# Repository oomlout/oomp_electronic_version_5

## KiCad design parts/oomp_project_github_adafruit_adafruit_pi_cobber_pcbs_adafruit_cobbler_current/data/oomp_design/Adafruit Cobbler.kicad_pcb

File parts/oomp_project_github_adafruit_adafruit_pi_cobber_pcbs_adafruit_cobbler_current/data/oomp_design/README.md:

# OOMP KiCad design copy

Open `Adafruit Cobbler.kicad_pro` (or the `.kicad_pcb` / `.kicad_sch`) in KiCad. Local OOMP libraries are under `libraries/`. Original inputs are preserved in [../original/](../original/).

Only verified unchanged installed KiCad defaults were renamed. Modified, custom, unmatched and unavailable items remain unchanged. Soldering variants are never swapped during conversion. Existing pad coordinates, nets and UUIDs are preserved.

See [conversion_report.yaml](conversion_report.yaml) for every conversion and skip. Copy this directory before editing; regeneration refuses to overwrite edited design files.

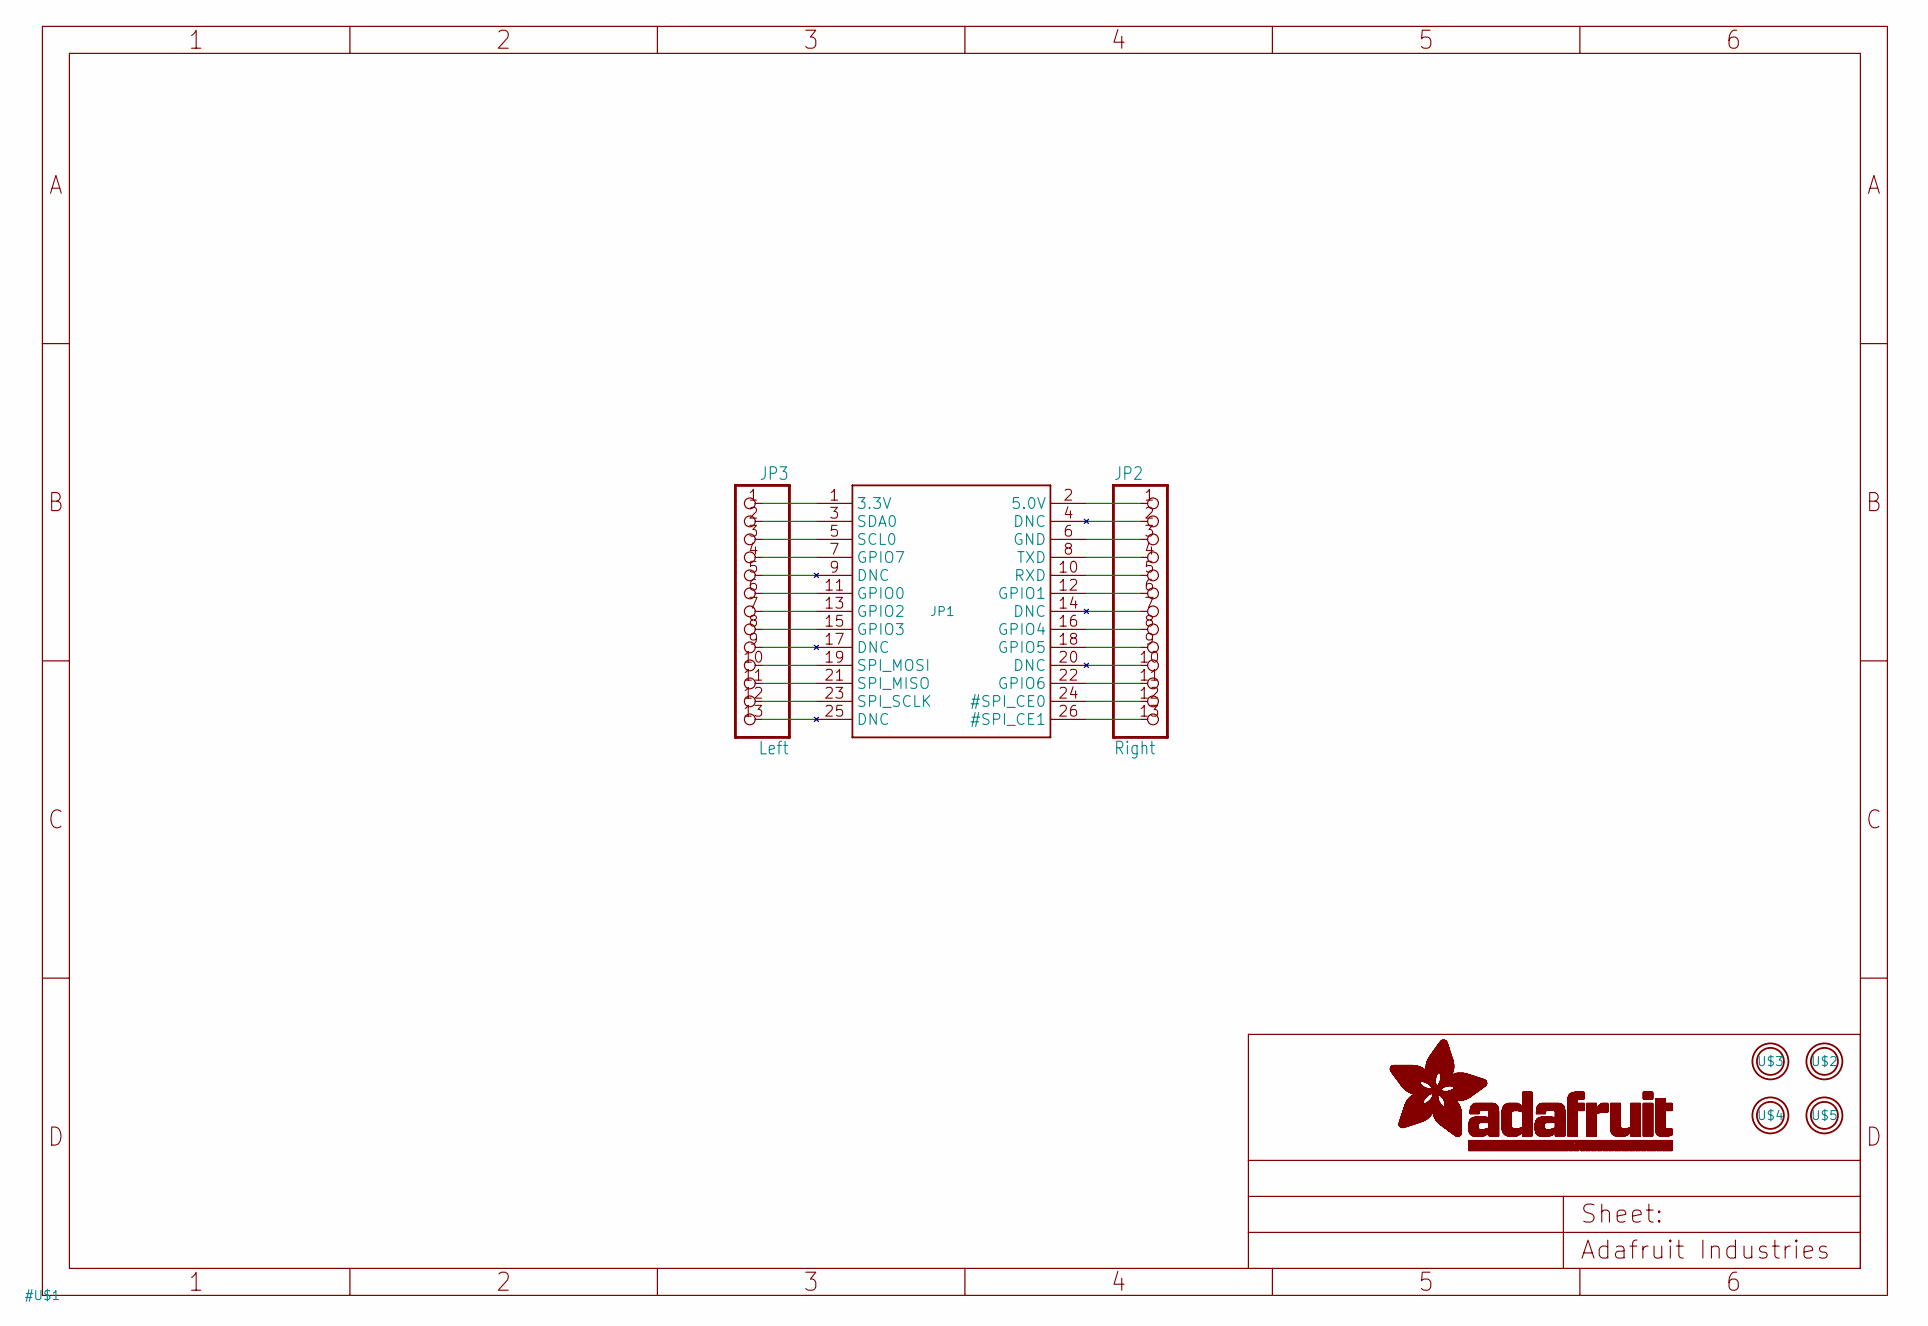
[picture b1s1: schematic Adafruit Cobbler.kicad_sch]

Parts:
JP1: PI; RASBERRYPI_IDC
JP2: Right; 1X13_ROUND_76MIL
JP3: Left; 1X13_ROUND_76MIL
U$2, U$3, U$4, U$5: MOUNTINGHOLE2.5; MOUNTINGHOLE_2.5_PLATED

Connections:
3.3V: JP1.1 (3.3V), JP3.1
5.0V: JP1.2 (5.0V), JP2.1
GND: JP1.6 (GND), JP2.3
unnamed: JP1.3 (SDA0), JP3.2
unnamed: JP1.5 (SCL0), JP3.3
unnamed: JP1.7 (GPIO7), JP3.4
unnamed: JP1.9 (DNC), JP3.5
unnamed: JP1.11 (GPIO0), JP3.6
unnamed: JP1.13 (GPIO2), JP3.7
unnamed: JP1.15 (GPIO3), JP3.8
unnamed: JP1.17 (DNC), JP3.9
unnamed: JP1.19 (SPI_MOSI), JP3.10
unnamed: JP1.21 (SPI_MISO), JP3.11
unnamed: JP1.23 (SPI_SCLK), JP3.12
unnamed: JP1.25 (DNC), JP3.13
unnamed: JP1.4 (DNC), JP2.2
unnamed: JP1.8 (TXD), JP2.4
unnamed: JP1.10 (RXD), JP2.5
unnamed: JP1.12 (GPIO1), JP2.6
unnamed: JP1.14 (DNC), JP2.7
unnamed: JP1.16 (GPIO4), JP2.8
unnamed: JP1.18 (GPIO5), JP2.9
unnamed: JP1.20 (DNC), JP2.10
unnamed: JP1.22 (GPIO6), JP2.11
unnamed: JP1.24 (#SPI_CE0), JP2.12
unnamed: JP1.26 (#SPI_CE1), JP2.13

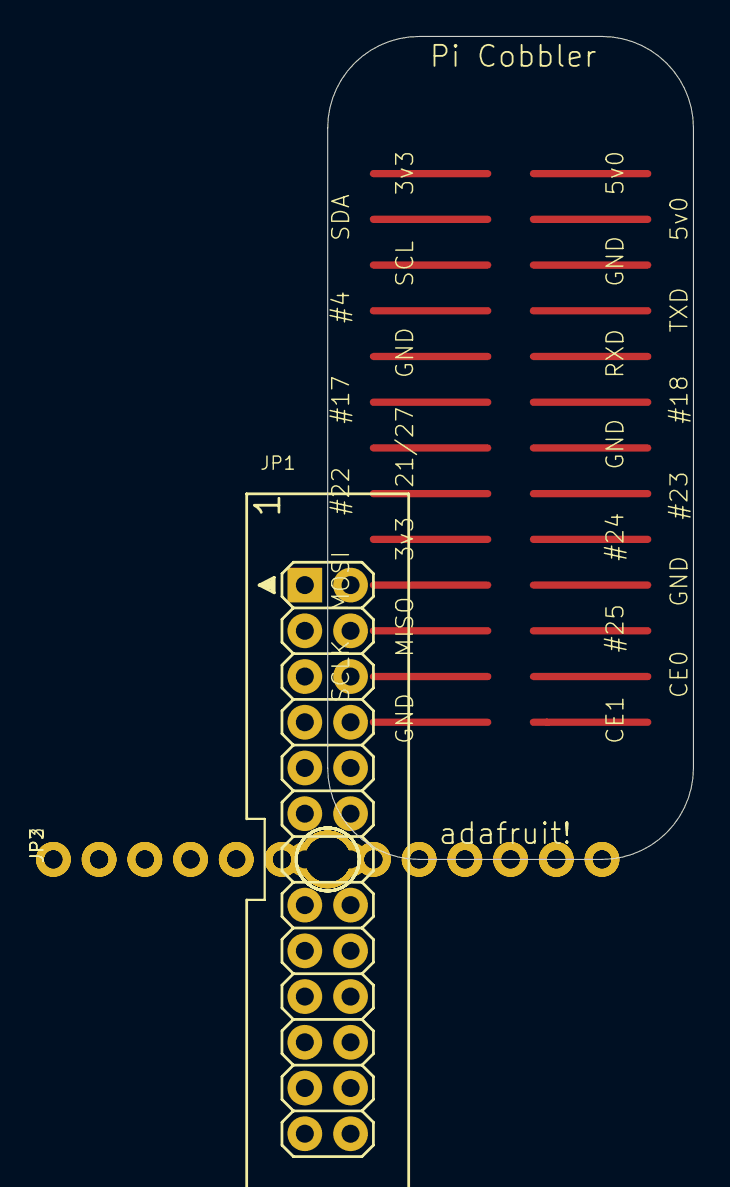
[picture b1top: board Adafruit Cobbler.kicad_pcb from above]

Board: 2 copper layers, 20.3 x 45.7 mm, 7 parts (0 on the bottom side), 26 nets.

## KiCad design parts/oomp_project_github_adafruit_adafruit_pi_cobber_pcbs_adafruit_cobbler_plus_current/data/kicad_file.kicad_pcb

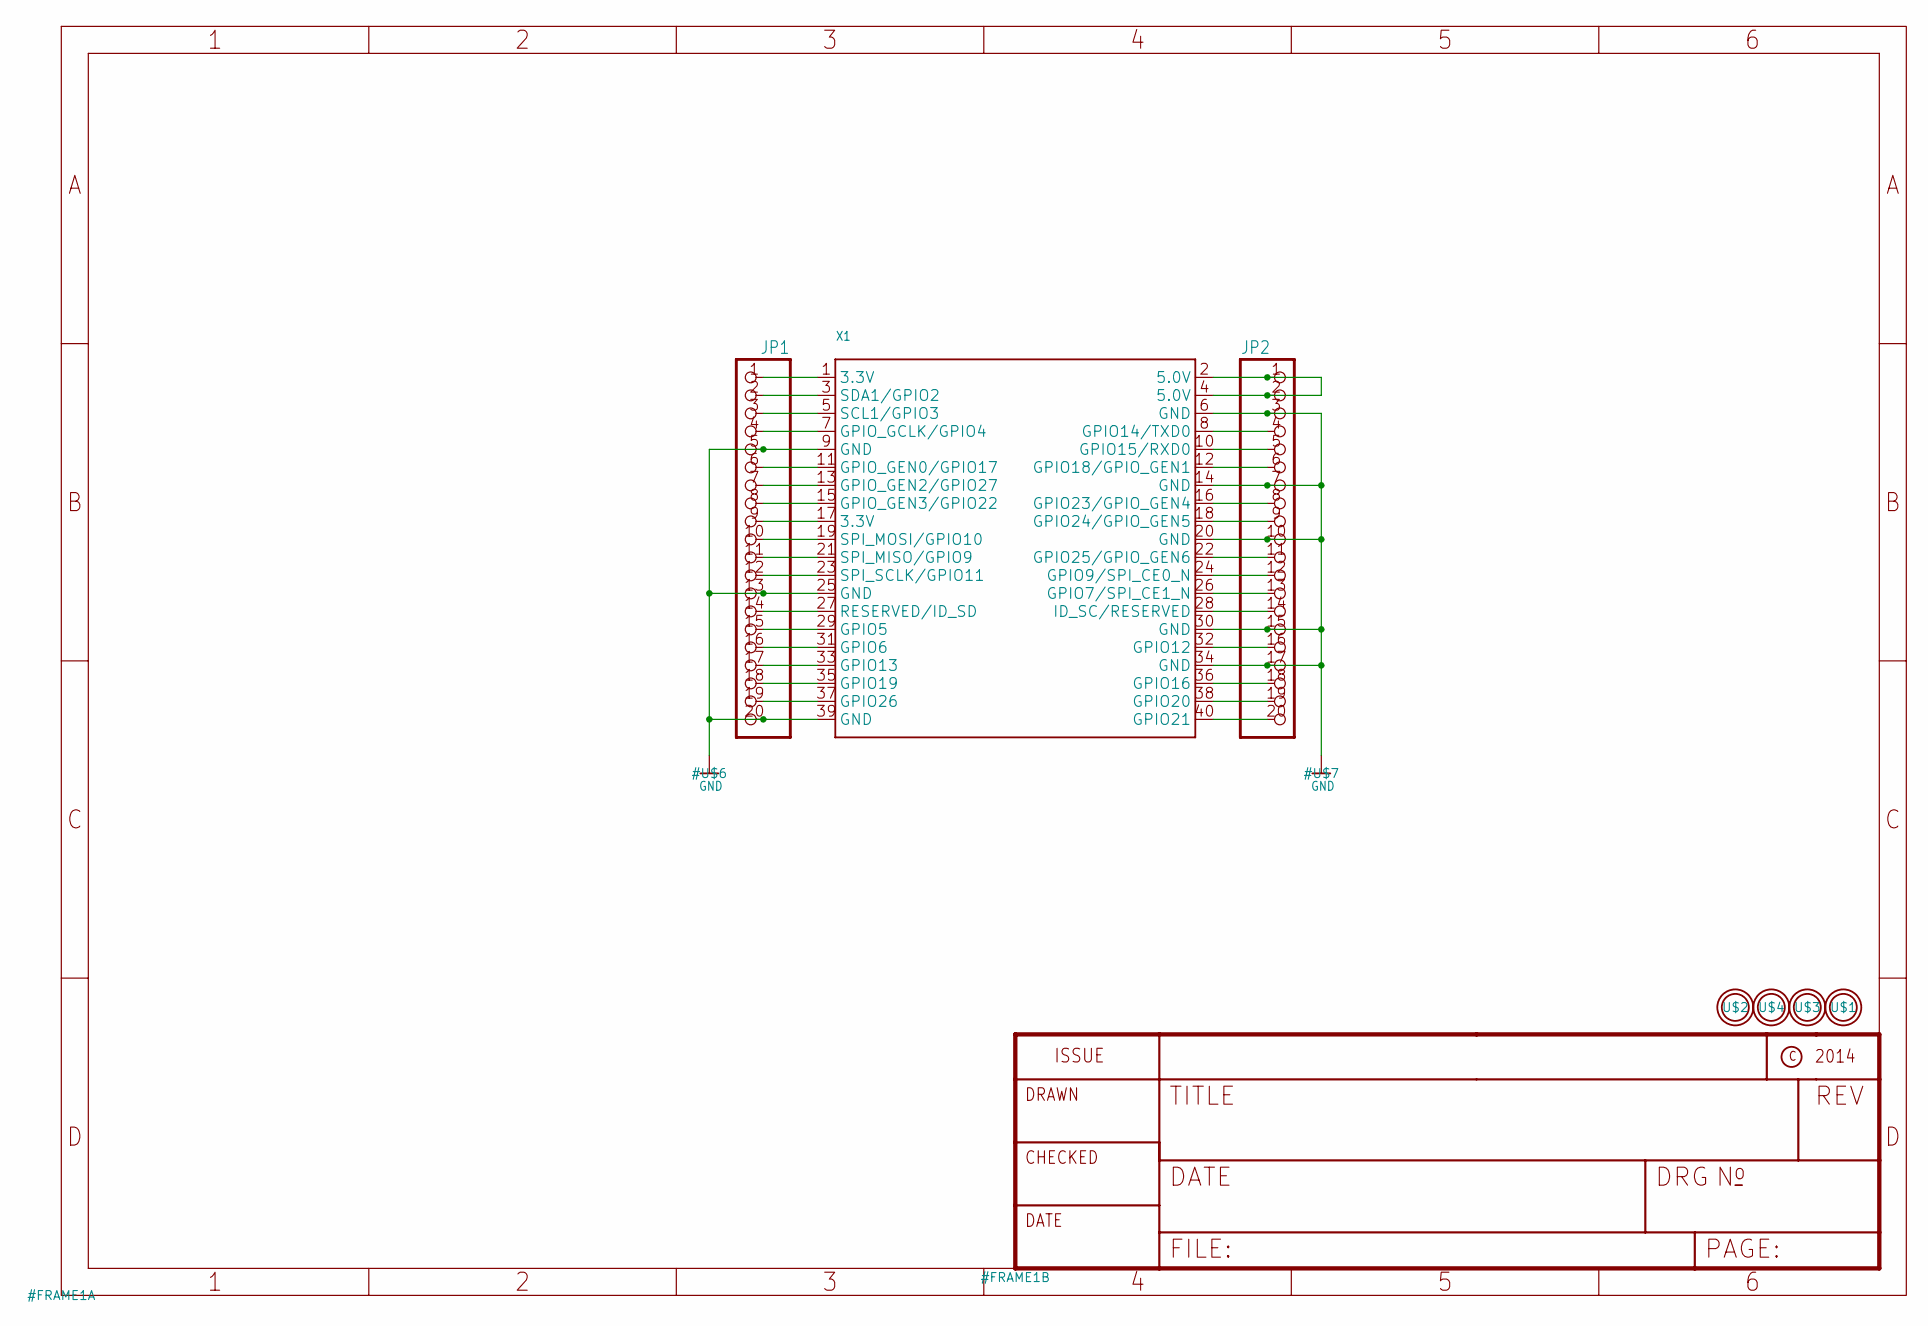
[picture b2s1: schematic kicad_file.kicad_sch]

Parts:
JP1, JP2: HEADER-1X20ROUND; 1X20_ROUND
U$1, U$2, U$3, U$4: MOUNTINGHOLE2.5_THICK; MOUNTINGHOLE_2.5_PLATED_THICK
X1: RASPBERRYPI_B+_IDC

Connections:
GND: JP1.5, JP1.13, JP1.20, JP2.3, JP2.7, JP2.10, JP2.15, JP2.17, X1.6 (GND), X1.9 (GND), X1.14 (GND), X1.20 (GND), X1.25 (GND), X1.30 (GND), X1.34 (GND), X1.39 (GND)
unnamed: JP2.1, JP2.2, X1.2 (5.0V), X1.4 (5.0V)
unnamed: JP2.4, X1.8 (GPIO14/TXD0)
unnamed: JP2.5, X1.10 (GPIO15/RXD0)
unnamed: JP2.6, X1.12 (GPIO18/GPIO_GEN1)
unnamed: JP2.8, X1.16 (GPIO23/GPIO_GEN4)
unnamed: JP2.9, X1.18 (GPIO24/GPIO_GEN5)
unnamed: JP2.11, X1.22 (GPIO25/GPIO_GEN6)
unnamed: JP2.12, X1.24 (GPIO9/SPI_CE0_N)
unnamed: JP2.13, X1.26 (GPIO7/SPI_CE1_N)
unnamed: JP2.14, X1.28 (ID_SC/RESERVED)
unnamed: JP2.16, X1.32 (GPIO12)
unnamed: JP2.18, X1.36 (GPIO16)
unnamed: JP2.19, X1.38 (GPIO20)
unnamed: JP2.20, X1.40 (GPIO21)
unnamed: JP1.1, X1.1 (3.3V)
unnamed: JP1.2, X1.3 (SDA1/GPIO2)
unnamed: JP1.3, X1.5 (SCL1/GPIO3)
unnamed: JP1.4, X1.7 (GPIO_GCLK/GPIO4)
unnamed: JP1.6, X1.11 (GPIO_GEN0/GPIO17)
unnamed: JP1.7, X1.13 (GPIO_GEN2/GPIO27)
unnamed: JP1.8, X1.15 (GPIO_GEN3/GPIO22)
unnamed: JP1.9, X1.17 (3.3V)
unnamed: JP1.10, X1.19 (SPI_MOSI/GPIO10)
unnamed: JP1.11, X1.21 (SPI_MISO/GPIO9)
unnamed: JP1.12, X1.23 (SPI_SCLK/GPIO11)
unnamed: JP1.14, X1.27 (RESERVED/ID_SD)
unnamed: JP1.15, X1.29 (GPIO5)
unnamed: JP1.16, X1.31 (GPIO6)
unnamed: JP1.17, X1.33 (GPIO13)
unnamed: JP1.18, X1.35 (GPIO19)
unnamed: JP1.19, X1.37 (GPIO26)

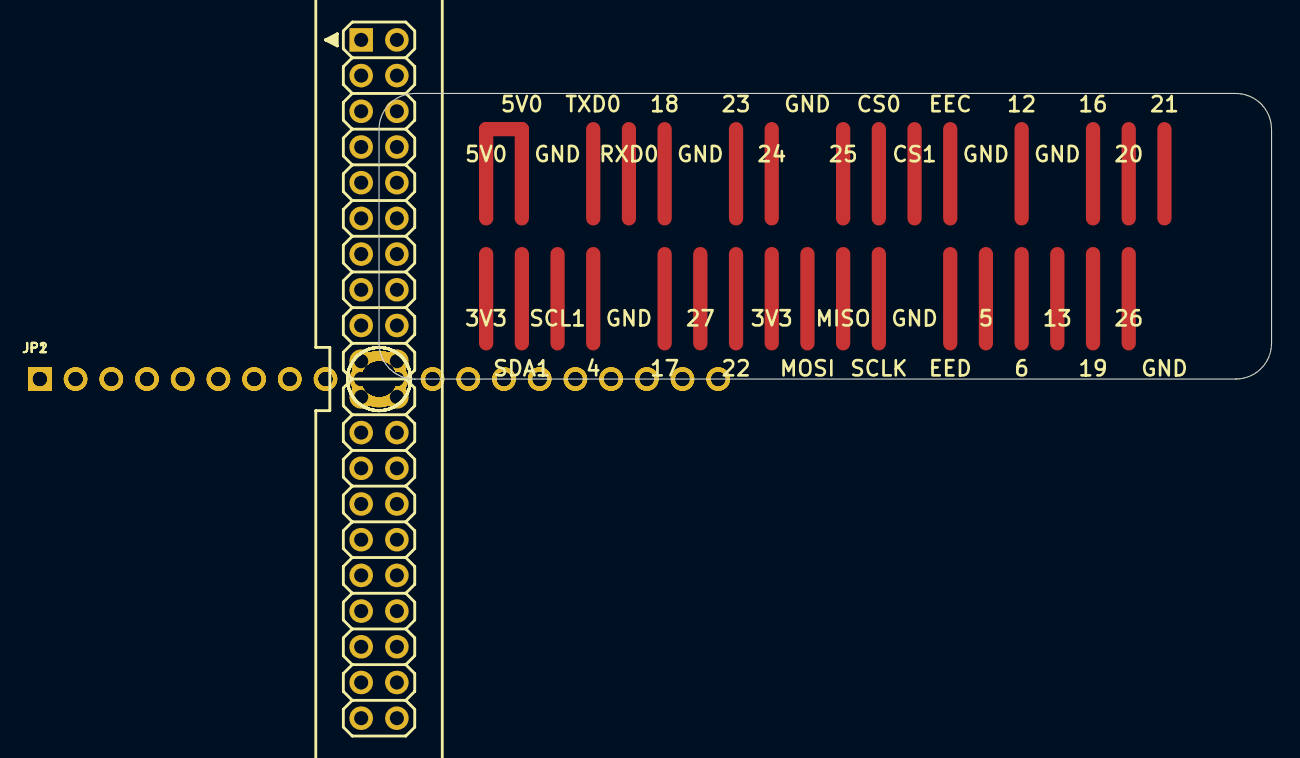
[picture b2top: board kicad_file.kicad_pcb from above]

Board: 2 copper layers, 63.5 x 20.3 mm, 7 parts (0 on the bottom side), 32 nets.

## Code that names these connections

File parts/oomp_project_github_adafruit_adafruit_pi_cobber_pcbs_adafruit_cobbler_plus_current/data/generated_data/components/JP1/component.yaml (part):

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      connected_to:
      - reference: X1
        pin_number: '3'
        pin_name: SDA1/GPIO2
    - number: '3'
      name: '3'
      electrical_type: passive
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      connected_to:
      - reference: X1
        pin_number: '5'
        pin_name: SCL1/GPIO3
    - number: '4'
      name: '4'
      electrical_type: passive
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      connected_to:
      - reference: X1
        pin_number: '7'
        pin_name: GPIO_GCLK/GPIO4
    - number: '5'
      name: '5'
      electrical_type: passive
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      connected_to:
      - reference: X1
        pin_number: '11'
        pin_name: GPIO_GEN0/GPIO17
    - number: '7'
      name: '7'
      electrical_type: passive
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      connected_to:
      - reference: X1
        pin_number: '13'
        pin_name: GPIO_GEN2/GPIO27
    - number: '8'
      name: '8'
      electrical_type: passive
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      connected_to:
      - reference: X1
        pin_number: '15'
        pin_name: GPIO_GEN3/GPIO22
    - number: '9'
      name: '9'
      electrical_type: passive
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      connected_to:
      - reference: X1
        pin_number: '19'
        pin_name: SPI_MOSI/GPIO10
    - number: '11'
      name: '11'
      electrical_type: passive
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      connected_to:
      - reference: X1
        pin_number: '21'
        pin_name: SPI_MISO/GPIO9
    - number: '12'
      name: '12'
      electrical_type: passive
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      connected_to:
      - reference: X1
        pin_number: '23'
        pin_name: SPI_SCLK/GPIO11
    - number: '13'
      name: '13'
      electrical_type: passive
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      connected_to:
      - reference: X1
        pin_number: '29'
        pin_name: GPIO5
    - number: '16'
      name: '16'
      electrical_type: passive
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      connected_to:
      - reference: X1
        pin_number: '31'
        pin_name: GPIO6
    - number: '17'
      name: '17'
      electrical_type: passive
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      connected_to:
      - reference: X1
        pin_number: '33'
        pin_name: GPIO13
    - number: '18'
      name: '18'
      electrical_type: passive
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      connected_to:
      - reference: X1
        pin_number: '35'
        pin_name: GPIO19
    - number: '19'
      name: '19'
      electrical_type: passive
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      connected_to:
      - reference: X1
        pin_number: '37'
        pin_name: GPIO26
    - number: '20'
      name: '20'
      electrical_type: passive
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    pin_name: 3.3V
  - reference: X1
    pin_number: '11'
    pin_name: GPIO_GEN0/GPIO17
  - reference: X1
    pin_number: '13'
    pin_name: GPIO_GEN2/GPIO27
  - reference: X1
    pin_number: '14'
    pin_name: GND
  - reference: X1
    pin_number: '15'
    pin_name: GPIO_GEN3/GPIO22
  - reference: X1
    pin_number: '17'
    pin_name: 3.3V
  - reference: X1
    pin_number: '19'
    pin_name: SPI_MOSI/GPIO10
  - reference: X1
    pin_number: '20'
    pin_name: GND
  - reference: X1
    pin_number: '21'
    pin_name: SPI_MISO/GPIO9
  - reference: X1
    pin_number: '23'
    pin_name: SPI_SCLK/GPIO11
  - reference: X1
    pin_number: '25'
    pin_name: GND
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    pin_name: RESERVED/ID_SD
  - reference: X1
    pin_number: '29'
    pin_name: GPIO5
  - reference: X1
    pin_number: '3'
    pin_name: SDA1/GPIO2
  - reference: X1
    pin_number: '30'
    pin_name: GND
  - reference: X1
    pin_number: '31'
    pin_name: GPIO6
  - reference: X1
    pin_number: '33'
    pin_name: GPIO13
  - reference: X1
    pin_number: '34'
    pin_name: GND
  - reference: X1
    pin_number: '35'
    pin_name: GPIO19
  - reference: X1
    pin_number: '37'
    pin_name: GPIO26
  - reference: X1
    pin_number: '39'
    pin_name: GND
  - reference: X1
    pin_number: '5'
    pin_name: SCL1/GPIO3
  - reference: X1
    pin_number: '6'
    pin_name: GND
  - reference: X1
    pin_number: '7'
    pin_name: GPIO_GCLK/GPIO4
  - reference: X1
    pin_number: '9'
    pin_name: GND
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
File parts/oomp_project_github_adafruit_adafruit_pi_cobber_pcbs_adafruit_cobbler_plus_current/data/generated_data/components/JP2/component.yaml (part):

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      connected_to:
      - reference: X1
        pin_number: '8'
        pin_name: GPIO14/TXD0
    - number: '5'
      name: '5'
      electrical_type: passive
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      connected_to:
      - reference: X1
        pin_number: '10'
        pin_name: GPIO15/RXD0
    - number: '6'
      name: '6'
      electrical_type: passive
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      connected_to:
      - reference: X1
        pin_number: '12'
        pin_name: GPIO18/GPIO_GEN1
    - number: '7'
      name: '7'
      electrical_type: passive
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      connected_to:
      - reference: X1
        pin_number: '16'
        pin_name: GPIO23/GPIO_GEN4
    - number: '9'
      name: '9'
      electrical_type: passive
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      connected_to:
      - reference: X1
        pin_number: '18'
        pin_name: GPIO24/GPIO_GEN5
    - number: '10'
      name: '10'
      electrical_type: passive
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      connected_to:
      - reference: X1
        pin_number: '22'
        pin_name: GPIO25/GPIO_GEN6
    - number: '12'
      name: '12'
      electrical_type: passive
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      connected_to:
      - reference: X1
        pin_number: '24'
        pin_name: GPIO9/SPI_CE0_N
    - number: '13'
      name: '13'
      electrical_type: passive
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      connected_to:
      - reference: X1
        pin_number: '26'
        pin_name: GPIO7/SPI_CE1_N
    - number: '14'
      name: '14'
      electrical_type: passive
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      connected_to:
      - reference: X1
        pin_number: '32'
        pin_name: GPIO12
    - number: '17'
      name: '17'
      electrical_type: passive
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      connected_to:
      - reference: X1
        pin_number: '36'
        pin_name: GPIO16
    - number: '19'
      name: '19'
      electrical_type: passive
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      connected_to:
      - reference: X1
        pin_number: '38'
        pin_name: GPIO20
    - number: '20'
      name: '20'
      electrical_type: passive
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      connected_to:
      - reference: X1
        pin_number: '40'
        pin_name: GPIO21
    size:
      local_graphics:
        measurement: symbol graphics only; excludes pins, properties, and text
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    pin_name: '7'
  - reference: X1
    pin_number: '10'
    pin_name: GPIO15/RXD0
  - reference: X1
    pin_number: '12'
    pin_name: GPIO18/GPIO_GEN1
  - reference: X1
    pin_number: '14'
    pin_name: GND
  - reference: X1
    pin_number: '16'
    pin_name: GPIO23/GPIO_GEN4
  - reference: X1
    pin_number: '18'
    pin_name: GPIO24/GPIO_GEN5
  - reference: X1
    pin_number: '2'
    pin_name: 5.0V
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    pin_name: GND
  - reference: X1
    pin_number: '22'
    pin_name: GPIO25/GPIO_GEN6
  - reference: X1
    pin_number: '24'
    pin_name: GPIO9/SPI_CE0_N
  - reference: X1
    pin_number: '25'
    pin_name: GND
  - reference: X1
    pin_number: '26'
    pin_name: GPIO7/SPI_CE1_N
  - reference: X1
    pin_number: '28'
    pin_name: ID_SC/RESERVED
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    pin_name: GND
  - reference: X1
    pin_number: '32'
    pin_name: GPIO12
  - reference: X1
    pin_number: '34'
    pin_name: GND
  - reference: X1
    pin_number: '36'
    pin_name: GPIO16
  - reference: X1
    pin_number: '38'
    pin_name: GPIO20
  - reference: X1
    pin_number: '39'
    pin_name: GND
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    pin_name: 5.0V
  - reference: X1
    pin_number: '40'
    pin_name: GPIO21
  - reference: X1
    pin_number: '6'
    pin_name: GND
  - reference: X1
    pin_number: '8'
    pin_name: GPIO14/TXD0
  - reference: X1
    pin_number: '9'
    pin_name: GND
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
